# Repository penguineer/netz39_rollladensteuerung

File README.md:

# Rolladensteuerung

## Content

- controller:       Relais-Controller Rollläden
- manuellsteuerung: Schalter für Manuellbetrieb Rollläden
- raspberry:        Software für den Kontroll-Raspy
- relaiskarte:      Relais Rollläden
- switchboard:      Altes Schalterboard
- tuer-controller:  I2C-Bridge zur Tür-Steuerung
- tuer-steuerung:   Kontrolle Motor und Türstatus-Schalter
- wd-switch:        Watchdog-Switch für Reset per Raspy-

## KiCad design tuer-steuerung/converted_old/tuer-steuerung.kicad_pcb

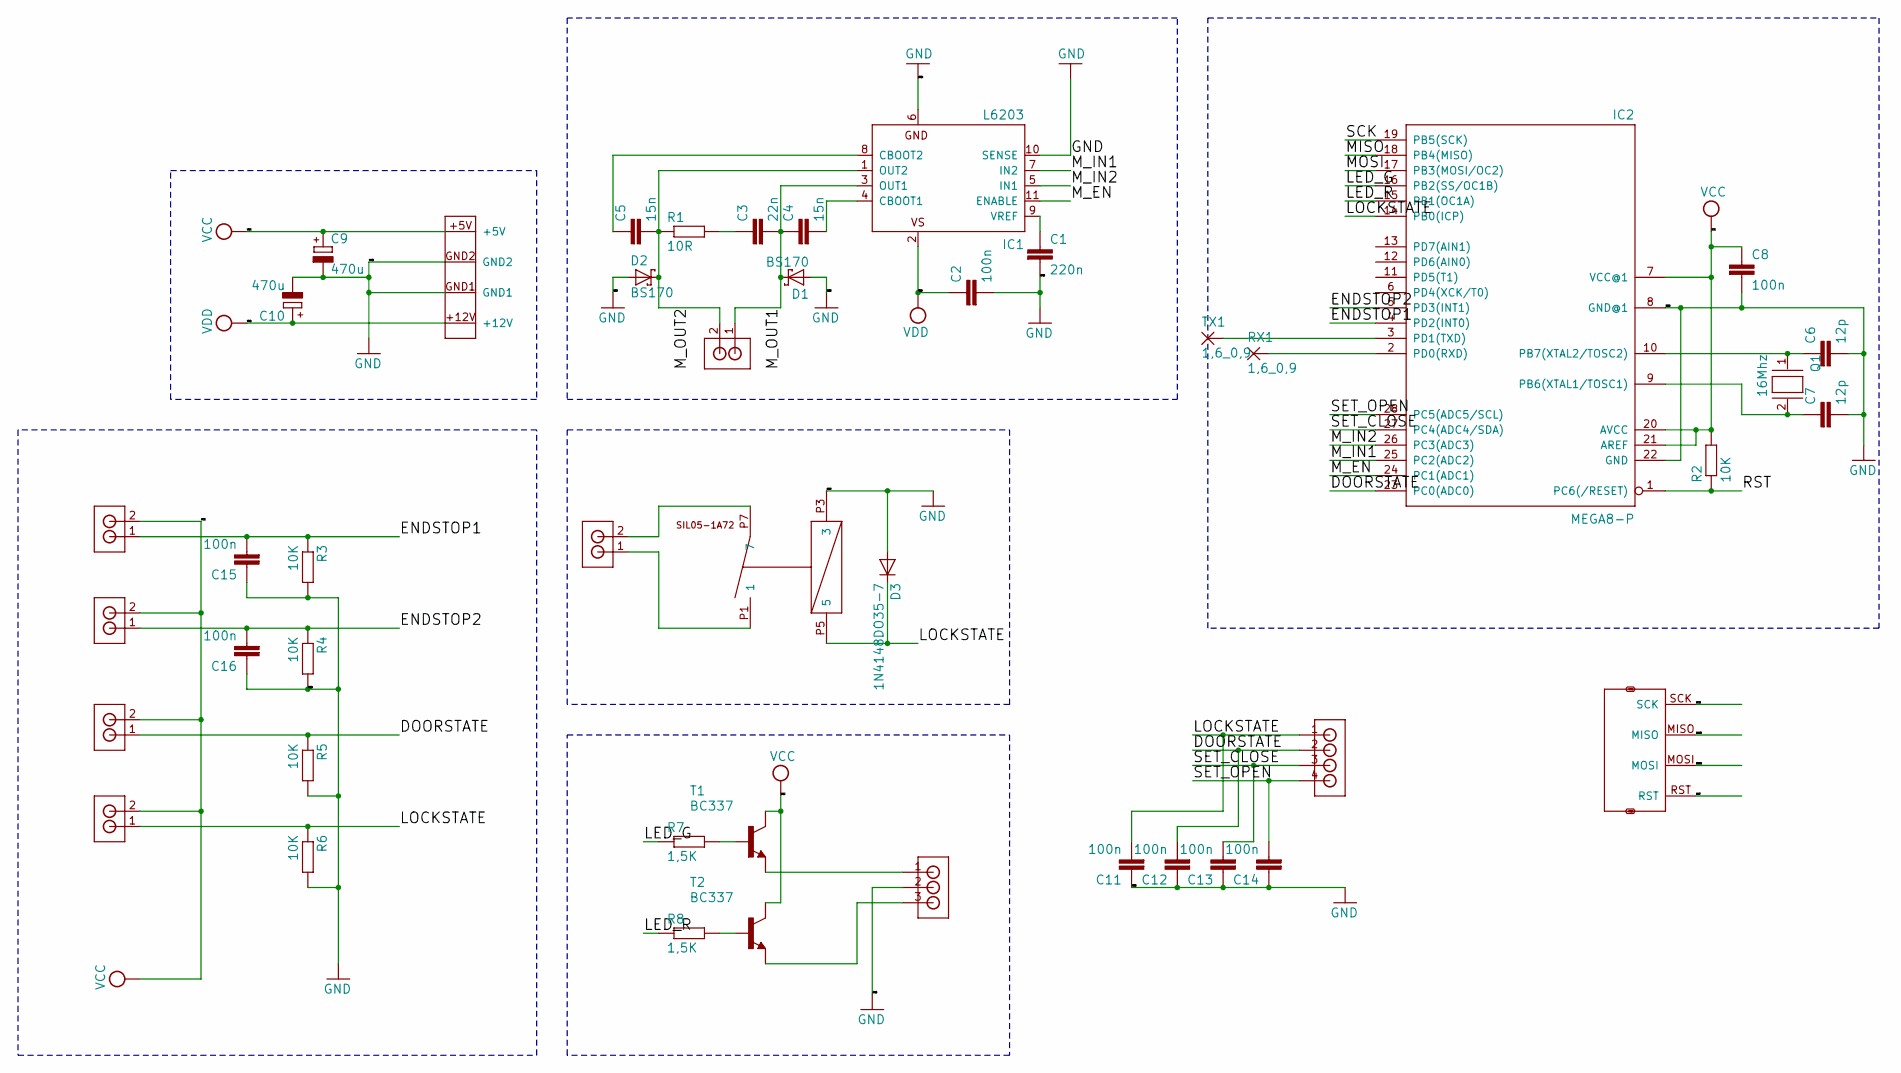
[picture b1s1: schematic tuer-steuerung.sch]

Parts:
C1: 220n; C025-024X044
C2, C8, C11, C12, C13, C14, C15, C16: 100n; C025-024X044
C3: 22n; C025-024X044
C4: 15n; C025-024X044
C5: 15n; C050-024X044
C6, C7: 12p; C050-025X075
C9, C10: 470u; TAP5-80
D1, D2: BS170; DO35-7
D3: 1N4148DO35-7; DO35-7
DOORSTATE1: RIACON_101_2
ENDSTOP1, ENDSTOP2: RIACON_101_2
IC1: L6203; MULTIWATT-11
IC2: MEGA8-P; DIL28-3
LOCKSTATE1: RIACON_101_2
MOTOR1: RIACON_101_2
NERDSTERN1: RIACON_101_2
Q1: 16Mhz; QS
R1: 10R; 0207_5V
R2, R3, R4, R5, R6: 10K; 0204_5
R7, R8: 1,5K; 0204_5
RX1: 1,6_0,9
T1, T2: BC337; TO92
TX1: 1,6_0,9
U$1: PSW_5
U$2: SIL05-1A72
U$3: AVR_ISP
U$4: RIACON_101_3
U$5: RIACON_101_4

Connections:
/DOORSTATE: C12.2, DOORSTATE1.1, IC2.23 (PC0(ADC0)), R5.1, U$5.2
/ENDSTOP1: C15.2, ENDSTOP1.1, IC2.4 (PD2(INT0)), R3.1
/ENDSTOP2: C16.2, ENDSTOP2.1, IC2.5 (PD3(INT1)), R4.1
/LED_G: IC2.16 (PB2(SS/OC1B)), R7.1
/LED_R: IC2.15 (PB1(OC1A)), R8.1
/LOCKSTATE: C11.2, D3.C, IC2.14 (PB0(ICP)), LOCKSTATE1.1, R6.1, U$2.P5 (5), U$5.1
/MISO: IC2.18 (PB4(MISO)), U$3.MISO
/MOSI: IC2.17 (PB3(MOSI/OC2)), U$3.MOSI
/M_EN: IC1.11 (ENABLE), IC2.24 (PC1(ADC1))
/M_IN1: IC1.7 (IN2), IC2.25 (PC2(ADC2))
/M_IN2: IC1.5 (IN1), IC2.26 (PC3(ADC3))
/M_OUT1: C3.2, C4.1, D1.C, IC1.3 (OUT1), MOTOR1.1
/M_OUT2: C5.2, D2.C, IC1.1 (OUT2), MOTOR1.2, R1.1
/RST: IC2.1 (PC6(/RESET)), R2.1, U$3.RST
/SCK: IC2.19 (PB5(SCK)), U$3.SCK
/SET_CLOSE: C13.2, IC2.27 (PC4(ADC4/SDA)), U$5.3
/SET_OPEN: C14.2, IC2.28 (PC5(ADC5/SCL)), U$5.4
GND: C1.2, C2.2, C6.2, C7.2, C8.2, C9.-, C10.-, C11.1, C12.1, C13.1, C14.1, C15.1, C16.1, D1.A, D2.A, D3.A, IC1.6 (GND), IC1.10 (SENSE), IC2.8 (GND@1), IC2.22 (GND), R3.2, R4.2, R5.2, R6.2, U$1.GND1, U$1.GND2, U$2.P3 (3), U$3.GND, U$4.2
unnamed: C1.1, IC1.9 (VREF)
unnamed: C3.1, R1.2
unnamed: C4.2, IC1.4 (CBOOT1)
unnamed: C5.1, IC1.8 (CBOOT2)
unnamed: C6.1, IC2.10 (PB7(XTAL2/TOSC2)), Q1.1
unnamed: C7.1, IC2.9 (PB6(XTAL1/TOSC1)), Q1.2
unnamed: IC2.2 (PD0(RXD)), RX1.1
unnamed: IC2.3 (PD1(TXD)), TX1.1
unnamed: NERDSTERN1.1, U$2.P1 (1)
unnamed: NERDSTERN1.2, U$2.P7 (7)
unnamed: R7.2, T1.2 (B)
unnamed: R8.2, T2.2 (B)
unnamed: T1.1 (E), U$4.1
unnamed: T2.1 (E), U$4.3
VCC: C8.1, C9.+, DOORSTATE1.2, ENDSTOP1.2, ENDSTOP2.2, IC2.7 (VCC@1), IC2.20 (AVCC), IC2.21 (AREF), LOCKSTATE1.2, R2.2, T1.3 (C), T2.3 (C), U$1.+5V, U$3.VCC
VDD: C2.1, C10.+, IC1.2 (VS), U$1.+12V

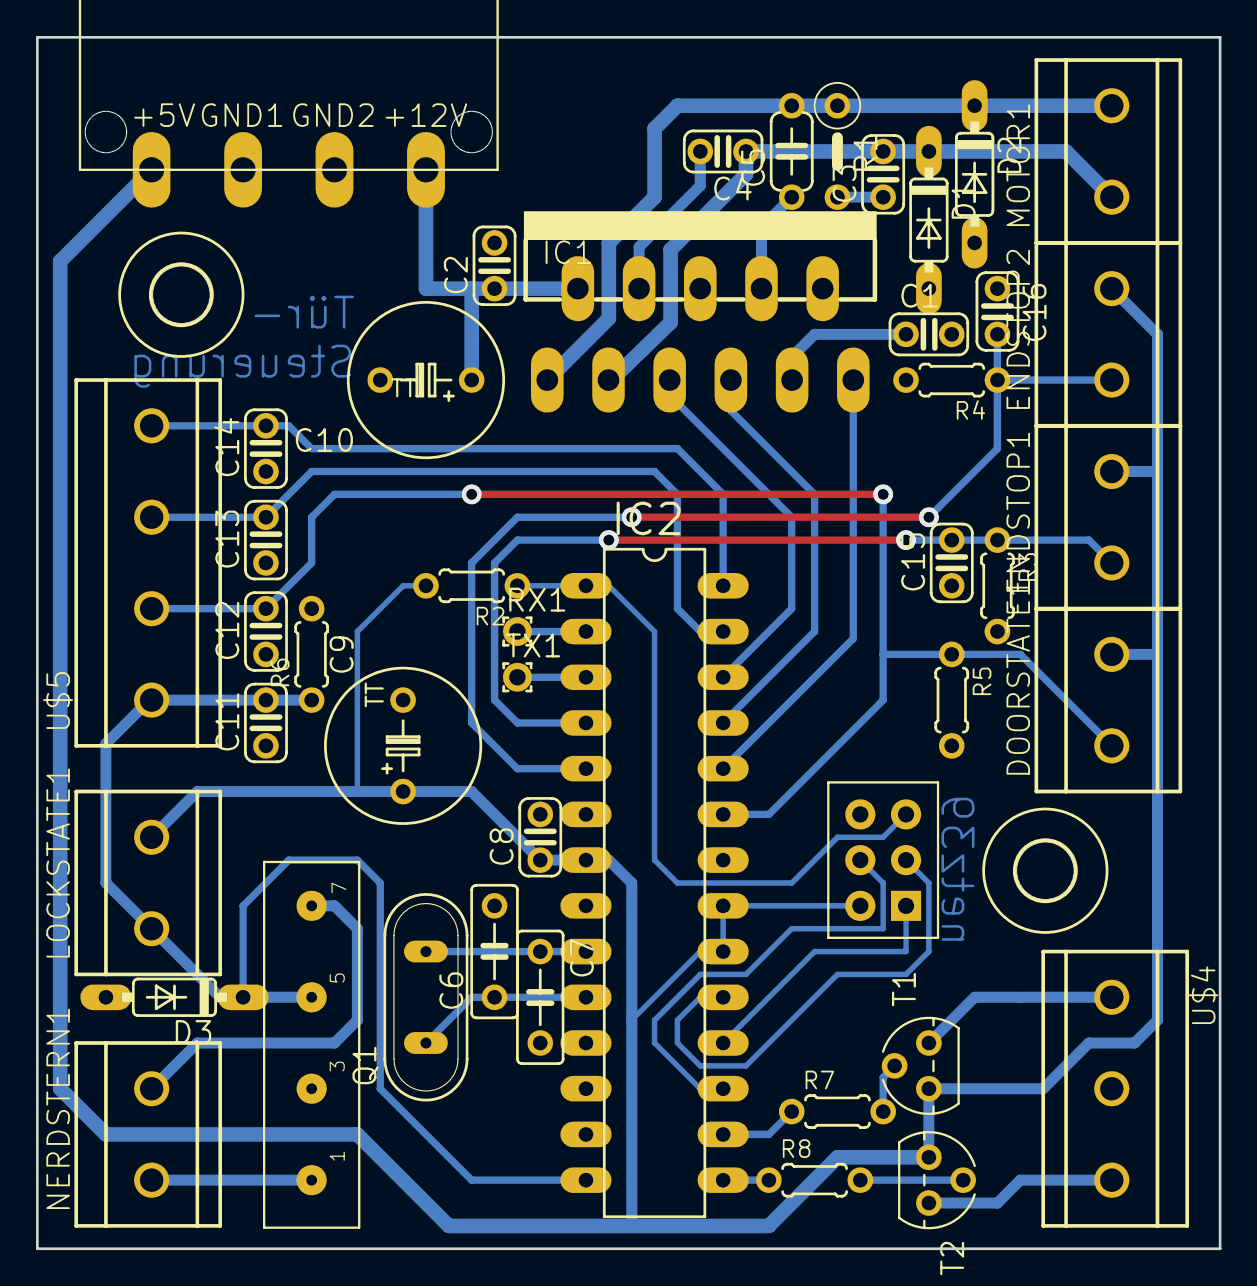
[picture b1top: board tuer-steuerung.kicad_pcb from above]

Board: 2 copper layers, 65.7 x 67.3 mm, 47 parts (0 on the bottom side), 34 nets.

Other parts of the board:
U$6, U$7: 3,2

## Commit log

2017-02-01 Send Door & Lock state changes as separate topics
2018-11-18 Converted eagle pcb and schematic to kicad, moved to converted_old
2018-11-18 added l6203 motor driver footprint, symbol
2018-11-18 added at90can128 datasheets
2018-11-18 Added many schematic sheets with basic structure and many todo texts
2018-11-22 Remove KiCAD backup files
    Fixes: 8c04058d9f3fa0f4235e588c12f971bd110264bf
2018-11-22 Revise Git ignore lists
    * split up into per folder
    * use special KiCAD ignore list from https://github.com/github/gitignore
    Suggested-by: David Kilias <david.kilias@gmail.com>
2020-02-06 switch on/off for changed gpio pins
2020-08-18 Imported updated requirements for new door pcb
2021-03-01 Separate I2C write and read operations
2021-07-16 fix readme markdown
